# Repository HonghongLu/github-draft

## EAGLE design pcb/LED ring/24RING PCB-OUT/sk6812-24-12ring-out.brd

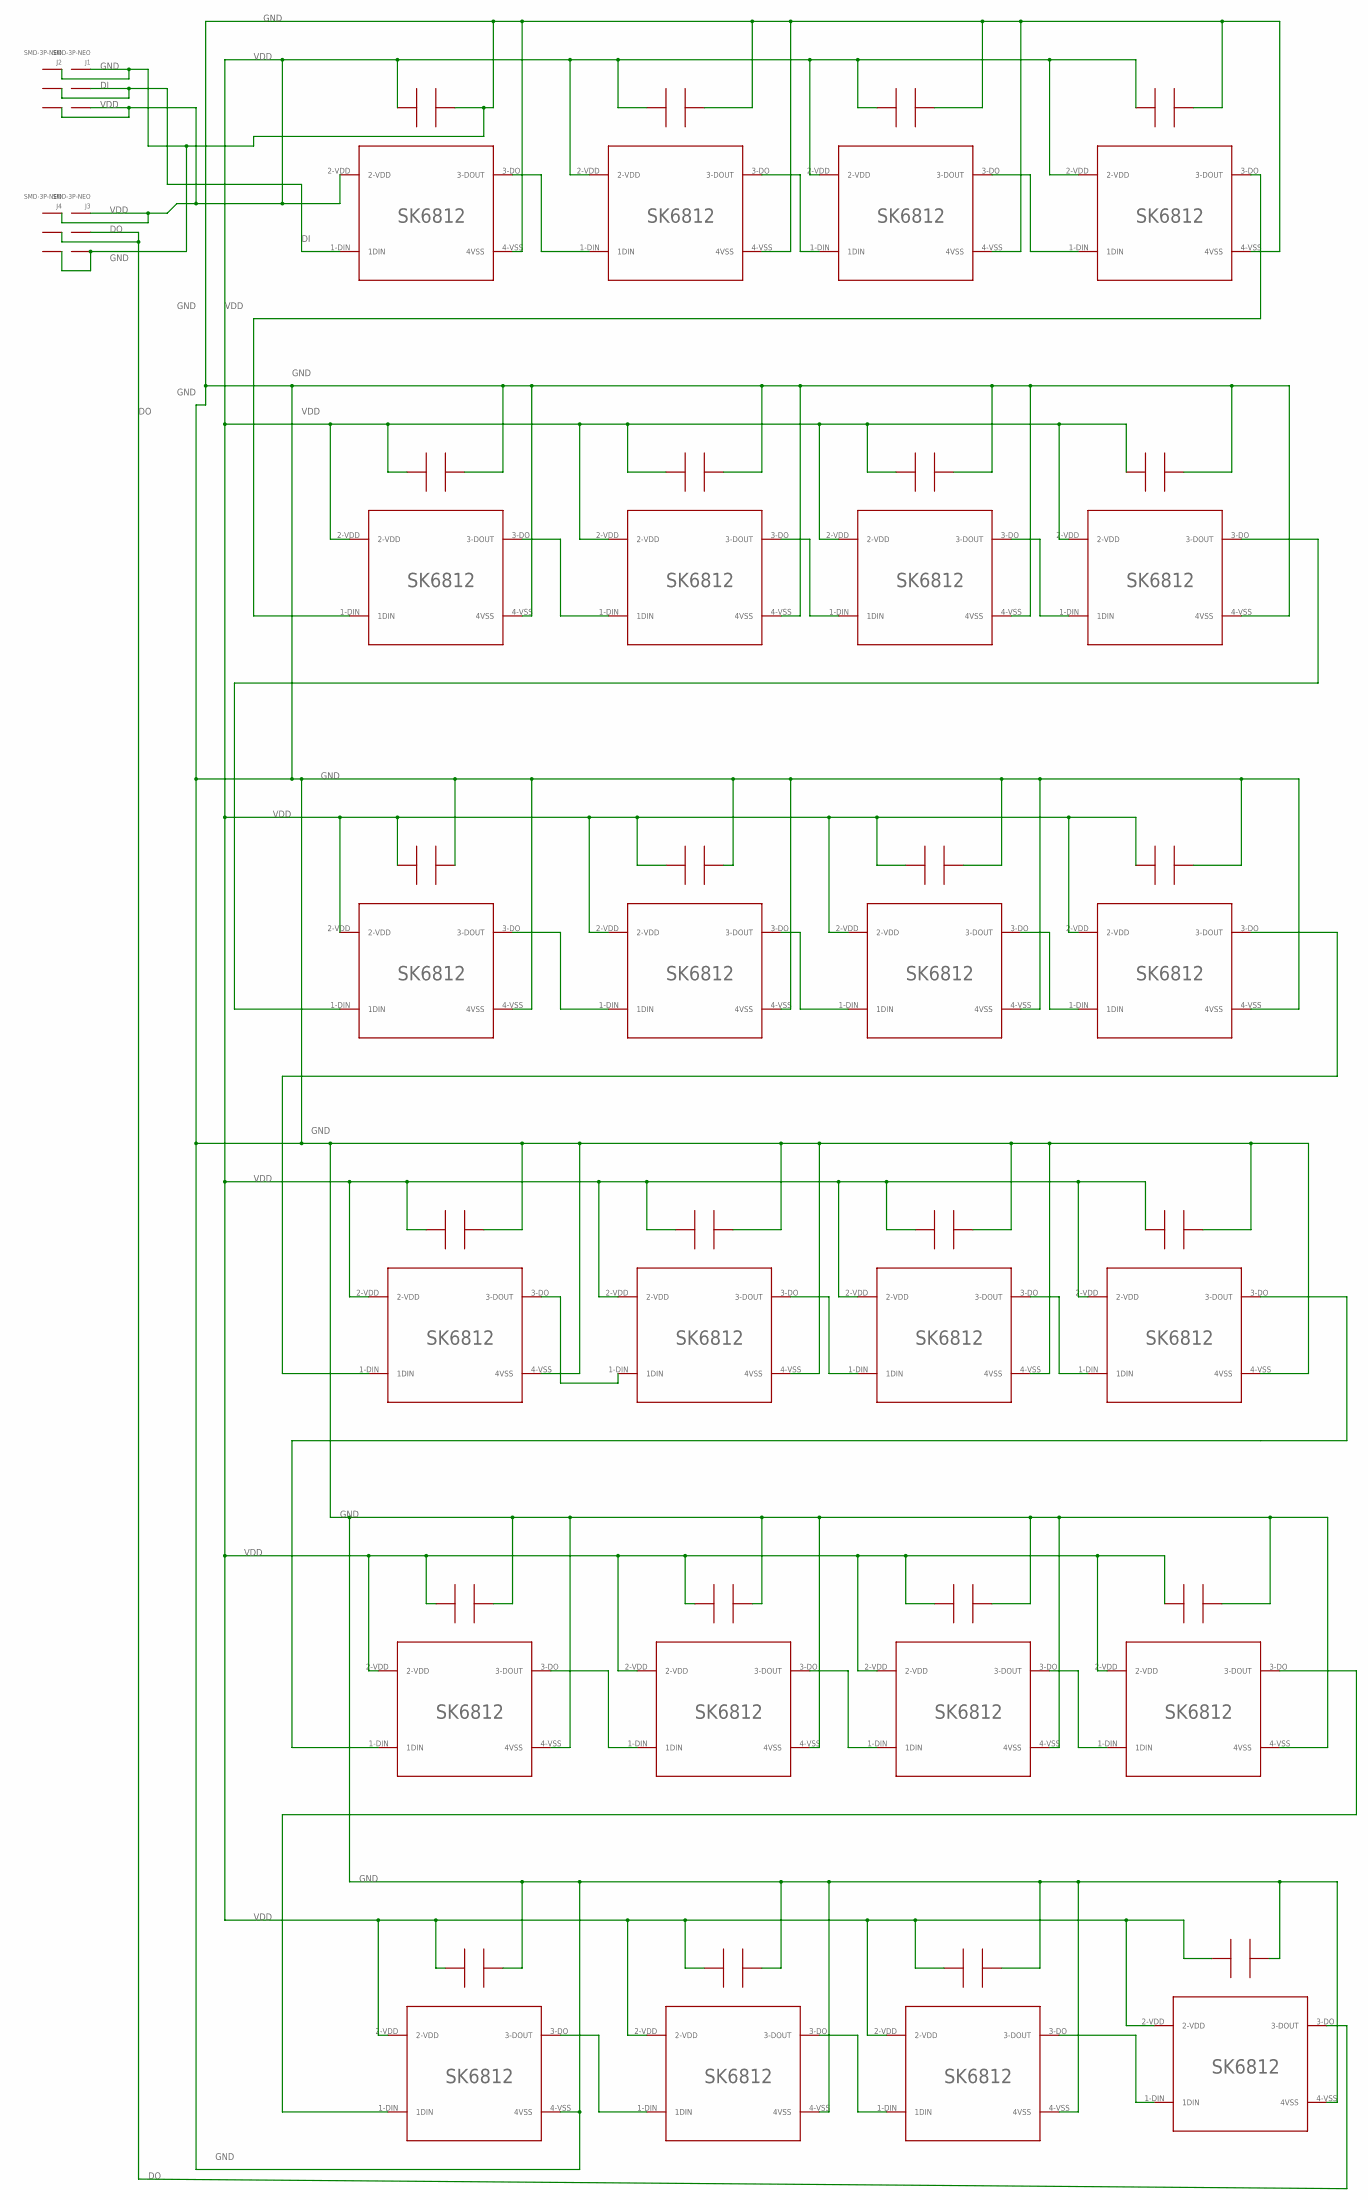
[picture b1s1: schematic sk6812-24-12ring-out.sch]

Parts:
D1, D2, D3, D4, D5, D6, D7, D8, D9, D10, D11, D12, D13, D14, D15, D16, D17, D18, D19, D20, D21, D22, D23, D24: SK6812-S-C; SMD4020+0402C
J1, J2, J3, J4: SMD-3P-NEO; SMD-3P-2.0

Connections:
DI: D1.1-DIN (1DIN), J1.P$2 (2), J2.P$2 (2)
DO: D24.3-DO (3-DOUT), J3.P$2 (2), J4.P$2 (2)
DO01: D1.3-DO (3-DOUT), D2.1-DIN (1DIN)
DO02: D2.3-DO (3-DOUT), D3.1-DIN (1DIN)
DO03: D3.3-DO (3-DOUT), D4.1-DIN (1DIN)
DO04: D4.3-DO (3-DOUT), D5.1-DIN (1DIN)
DO05: D5.3-DO (3-DOUT), D6.1-DIN (1DIN)
DO06: D6.3-DO (3-DOUT), D7.1-DIN (1DIN)
DO07: D7.3-DO (3-DOUT), D8.1-DIN (1DIN)
DO08: D8.3-DO (3-DOUT), D9.1-DIN (1DIN)
DO10: D10.3-DO (3-DOUT), D11.1-DIN (1DIN)
DO11: D11.3-DO (3-DOUT), D12.1-DIN (1DIN)
DO12: D12.3-DO (3-DOUT), D13.1-DIN (1DIN)
DO13: D13.3-DO (3-DOUT), D14.1-DIN (1DIN)
DO14: D14.3-DO (3-DOUT), D15.1-DIN (1DIN)
DO15: D15.3-DO (3-DOUT), D16.1-DIN (1DIN)
DO16: D16.3-DO (3-DOUT), D17.1-DIN (1DIN)
DO18: D18.3-DO (3-DOUT), D19.1-DIN (1DIN)
DO19: D19.3-DO (3-DOUT), D20.1-DIN (1DIN)
DO20: D20.3-DO (3-DOUT), D21.1-DIN (1DIN)
DO21: D21.3-DO (3-DOUT), D22.1-DIN (1DIN)
DO23: D23.3-DO (3-DOUT), D24.1-DIN (1DIN)
GND: D1.4-VSS (4VSS), D1.5-C-VSS (C-VSS), D2.4-VSS (4VSS), D2.5-C-VSS (C-VSS), D3.4-VSS (4VSS), D3.5-C-VSS (C-VSS), D4.4-VSS (4VSS), D4.5-C-VSS (C-VSS), D5.4-VSS (4VSS), D5.5-C-VSS (C-VSS), D6.4-VSS (4VSS), D6.5-C-VSS (C-VSS), D7.4-VSS (4VSS), D7.5-C-VSS (C-VSS), D8.4-VSS (4VSS), D8.5-C-VSS (C-VSS), D9.4-VSS (4VSS), D9.5-C-VSS (C-VSS), D10.4-VSS (4VSS), D10.5-C-VSS (C-VSS), D11.4-VSS (4VSS), D11.5-C-VSS (C-VSS), D12.4-VSS (4VSS), D12.5-C-VSS (C-VSS), D13.4-VSS (4VSS), D13.5-C-VSS (C-VSS), D14.4-VSS (4VSS), D14.5-C-VSS (C-VSS), D15.4-VSS (4VSS), D15.5-C-VSS (C-VSS), D16.4-VSS (4VSS), D16.5-C-VSS (C-VSS), D17.4-VSS (4VSS), D17.5-C-VSS (C-VSS), D18.4-VSS (4VSS), D18.5-C-VSS (C-VSS), D19.4-VSS (4VSS), D19.5-C-VSS (C-VSS), D20.4-VSS (4VSS), D20.5-C-VSS (C-VSS), D21.4-VSS (4VSS), D21.5-C-VSS (C-VSS), D22.4-VSS (4VSS), D22.5-C-VSS (C-VSS), D23.4-VSS (4VSS), D23.5-C-VSS (C-VSS), D24.4-VSS (4VSS), D24.5-C-VSS (C-VSS), J1.P$3 (3), J2.P$3 (3), J3.P$1 (1), J4.P$1 (1)
unnamed: D22.3-DO (3-DOUT), D23.1-DIN (1DIN)
unnamed: D17.3-DO (3-DOUT), D18.1-DIN (1DIN)
unnamed: D9.3-DO (3-DOUT), D10.1-DIN (1DIN)
VDD: D1.2-VDD, D1.6-C-VDD (C-VDD), D2.2-VDD, D2.6-C-VDD (C-VDD), D3.2-VDD, D3.6-C-VDD (C-VDD), D4.2-VDD, D4.6-C-VDD (C-VDD), D5.2-VDD, D5.6-C-VDD (C-VDD), D6.2-VDD, D6.6-C-VDD (C-VDD), D7.2-VDD, D7.6-C-VDD (C-VDD), D8.2-VDD, D8.6-C-VDD (C-VDD), D9.2-VDD, D9.6-C-VDD (C-VDD), D10.2-VDD, D10.6-C-VDD (C-VDD), D11.2-VDD, D11.6-C-VDD (C-VDD), D12.2-VDD, D12.6-C-VDD (C-VDD), D13.2-VDD, D13.6-C-VDD (C-VDD), D14.2-VDD, D14.6-C-VDD (C-VDD), D15.2-VDD, D15.6-C-VDD (C-VDD), D16.2-VDD, D16.6-C-VDD (C-VDD), D17.2-VDD, D17.6-C-VDD (C-VDD), D18.2-VDD, D18.6-C-VDD (C-VDD), D19.2-VDD, D19.6-C-VDD (C-VDD), D20.2-VDD, D20.6-C-VDD (C-VDD), D21.2-VDD, D21.6-C-VDD (C-VDD), D22.2-VDD, D22.6-C-VDD (C-VDD), D23.2-VDD, D23.6-C-VDD (C-VDD), D24.2-VDD, D24.6-C-VDD (C-VDD), J1.P$1 (1), J2.P$1 (1), J3.P$3 (3), J4.P$3 (3)

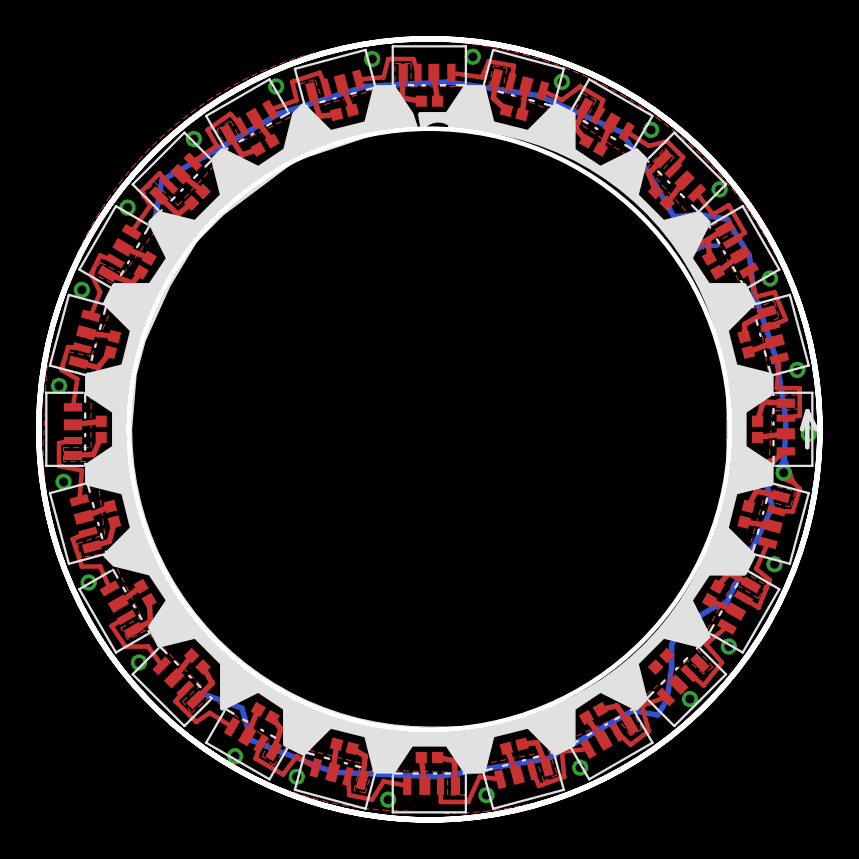
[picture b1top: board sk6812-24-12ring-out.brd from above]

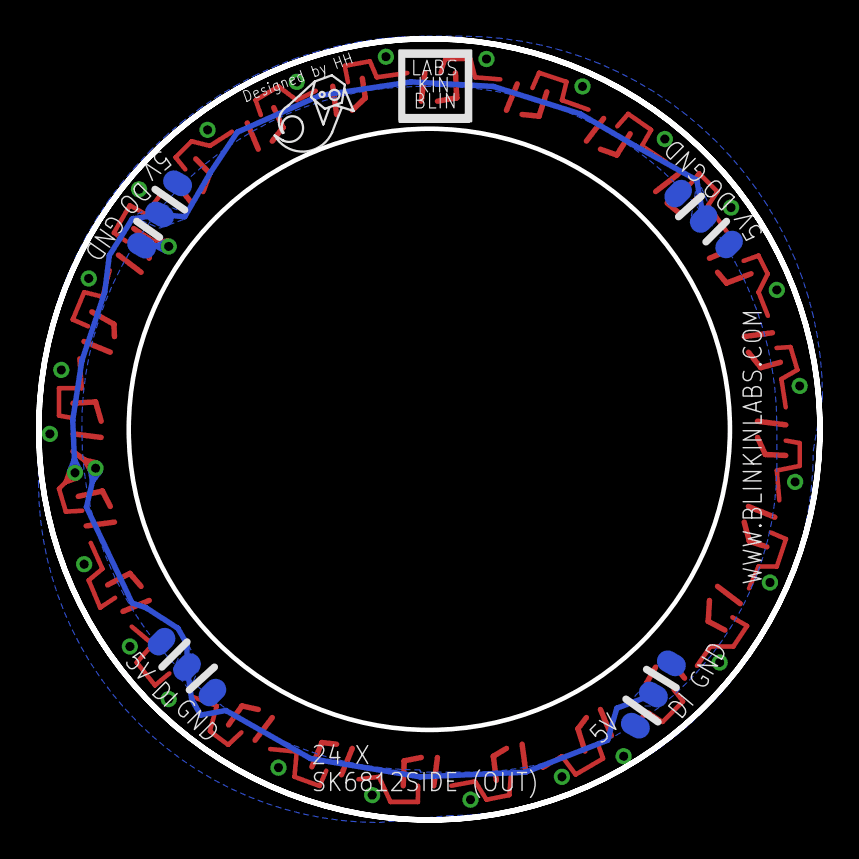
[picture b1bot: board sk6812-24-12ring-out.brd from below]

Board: 2 copper layers, 43.4 x 43.4 mm, 30 parts (6 on the bottom side), 27 nets.

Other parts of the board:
U$1: CRAZYCAT(M)
U$2: LOGO(M)

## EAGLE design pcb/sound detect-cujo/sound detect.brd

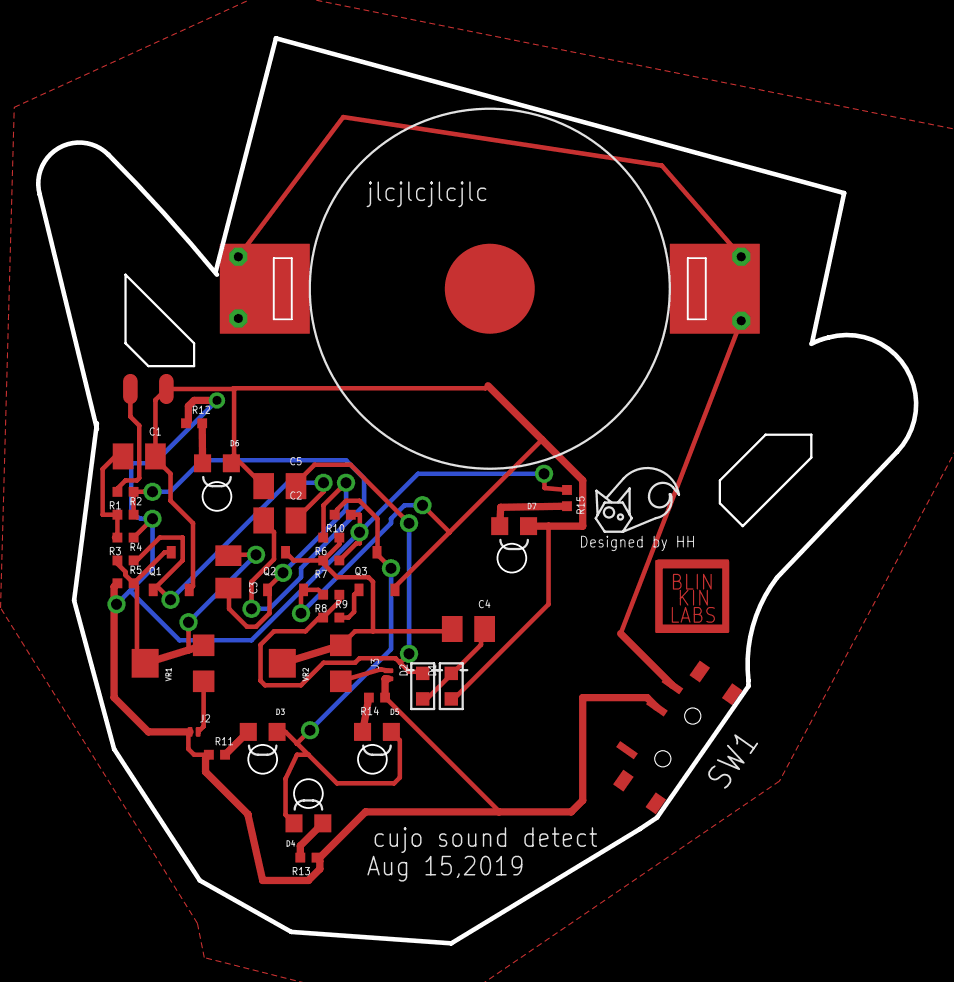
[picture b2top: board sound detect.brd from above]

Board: 2 copper layers, 48.8 x 50.3 mm, 40 parts (0 on the bottom side), 21 nets.

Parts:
C1: 10uF,0805; CAP-0805C-LEVELB
C2, C3, C4, C5: 1uF,0805; CAP-0805C-LEVELB
D1, D2: 1N4148-SOD523; SOD523
D3, D4, D5: 0603side-white; SMD-0603-LED-SIDE
D6, D7: 0603SIDELED-uv; SMD-0603-LED-SIDE
J1: SMD-PADS-2P; SMD-2P-2.0
J2, J3: SHORT_PAD; SHORTPAD
J4: CR2032-THR; CR2032-SMD
Q1, Q2, Q3: MMBT2222A; SOT23-3
R1, R2, R10: 1.2k,0402; RES-0402R-REFLOW
R3: 100R,0402; RES-0402R-REFLOW
R4, R6: 1M,0402; RES-0402R-REFLOW
R5, R7: 51k,0402; RES-0402R-REFLOW
R8: 100k,0402; RES-0402R-REFLOW
R9: 39k,0402; RES-0402R-REFLOW
R11, R12, R13, R14, R15: 510,0402; RES-0402R-REFLOW
SW1: SLIDE-MSK12C01-07; SLIDE-SW-MSK-12C01-07
U$2: CUJO(5050)-MASK-BOT
U$3: CRAZYCAT(M)
U$4: LOGO(M-T)
VR1, VR2: VG039NCHXTB204,200kVR; SMD-3638

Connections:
GND: C1.P$1, C5.P$2, D1.A, D6.C, D7.C, J1.P$1, J4.-, Q1.P$2, Q2.P$2, Q3.P$2, R8.P$1
MIC+: J1.P$2, R1.P$1
unnamed: C2.P$2, R1.P$2, R2.P$1
unnamed: C2.P$1, Q1.P$1, R4.P$1
unnamed: C3.P$1, Q2.P$1, R6.P$1
unnamed: C1.P$2, R2.P$2, R3.P$1
unnamed: J4.+, J4.+1, J4.++, J4.++1, J4.P$1, J4.P$2, J4.P$3, J4.P$4, SW1.POS2
unnamed: C4.P$1, D1.K, D2.A
unnamed: Q3.P$1, R9.P$1
unnamed: C5.P$1, D2.K, R8.P$2, R9.P$2
unnamed: C4.P$2, Q2.P$3, R6.P$2, R7.P$1, VR2.P$1, VR2.P$2
unnamed: D7.A, R15.P$1
unnamed: D3.C, D4.C, D5.C, Q3.P$3, R10.P$1
unnamed: D3.A, R11.P$1
unnamed: D6.A, R12.P$1
unnamed: D4.A, R13.P$1
unnamed: J2.P$1, VR1.P$3
unnamed: D5.A, R14.P$1
unnamed: C3.P$2, Q1.P$3, R4.P$2, R5.P$1, VR1.P$1, VR1.P$2
unnamed: J3.P$1, VR2.P$3
VCC: J2.P$2, J3.P$2, R3.P$2, R5.P$2, R7.P$2, R10.P$2, R11.P$2, R12.P$2, R13.P$2, R14.P$2, R15.P$2, SW1.COM

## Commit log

2017-10-25 just a holder for the pogo pins
    i printed it on up mini.
2017-11-04 this is the holder for blinkytile
    accessory: M3 screws
    stl file, up mini printed, 4minutes, material: pla.
    purpose: to hold the blinkytile pcb and mount it to the surface like wood etc...
2017-11-04 blinkytile holder photo
    blinkytile holder-M3 screw
2017-11-04 blinkytile_holder_holder 2-M3screws
    photos for the holder
2017-11-28 add file folder
2017-11-28 add folder
2018-01-06 add sk6812side*24ring pcb eagle files to led ring
    sk6812side pcb
    size 42*42mm
    product list
    face in
    https://shop.blinkinlabs.com/collections/leds/products/led-ring-with-24-right-angle-leds-inwards-facing
    face out
2018-10-16 move the files into 8by8 folder
2018-10-16 change the mounting holes location
2018-11-16 add 4mm cable maganet clip drawing
2018-11-16 rename
2019-02-01 milk frother stand
    it is designed to work with PRODUKT, Milk-frother from Ikea. I designed this tools for the frother work with most of the cups and glasses in my kitchen. https://www.instagram.com/p/BtU-5IWnOer/
2019-06-25 upload ring_out 3d drawing
2019-06-25 3d drawing
    upload the ring out 3d drawing
2019-06-25 ring_in_3d drawing
    upload 3d drawing
2019-06-25 drawing
    ring_out drawing in pdf
2019-06-25 drawing
    ring_in drawing in pdf
2019-06-25 drawing
    pdf drawing update
2019-06-25 drawing
    pdf drawing
2019-06-25 drawing
    drawing in pdf
2019-06-26 clip0626
    add support for the clip, snap the magnet instead glue it.
2019-08-22 Create sound detect cujo badge
2019-08-22 sound detect board
    sound detect board original from one part of toy circuit. It is analog circuit only.
2020-04-09 1.27-1.27-2X5
    1.27mm pitch to 1.27mm pitch, 2X5 pogo pin
    the pcb convert the 1.27 pogo pin to 2.54mm pitch to 2.54mm pitch 2X5 header.
    parts--
    pcb, 1.6mm(can be other thickness) FR4 HASL double layer
    R50-2W7, pogo pin socket solder on to the pcb
    P50-XX, pogo pins to push inside the pogo pin socket.
2020-04-09 1.27-1.27-2X5pogo pin photo
2020-12-02 Create led filament v1.step
    add filament 3d file
2020-12-02 Create led filament spec.pdf
    add filament datasheet
2021-01-13 add the reball stencil file for QL-EOS
    stencil thickness 0.2mm, normal laser cut. The stencil can work with the reball tool.
    BGA part:
    0.4mm pitch, 8*8 BGA, ball size 0.2mm or 0.25mm, recommend 0.2mm leadfree ball, hot plate process, remember use super thin flux on the BGA
2021-01-13 fdm printing 10mm strips holder for sofa
    LED Strip holder
2021-03-04 Create fusion file backup
2021-04-23 blinkytape controller stencil
    stencil frame: 250mm*250mm 5mm acrylic
    pcb panels: Rev I
2021-05-07 stencil frame
    stencil frame
2021-06-19 convert pc 120mm pc fan to solder Fume Extractor
    convert pc 120mm pc fan to solder Fume Extractor
2021-07-07 move the file into the folder
2021-07-12 add the 8X8 pixel images for reference
2021-07-14 add 18650 battery case
2021-07-16 add cat ear glasses
2021-07-21 add btc case 3d files
2021-07-26 add AAA case and fan stand
2021-07-26 case for the caliper
2021-08-02 add luzhanqi files
2021-09-29 add 3d files
2021-09-29 add btc pic
2021-11-16 add 1.27-2.0-2.54 pogo pin perfboard
    HASL with 0.8mm thickness
2023-01-08 add universal test rig_fdm printing parts drawing
    test jig is from https://www.aliexpress.com/item/1005001779451202.html?gatewayAdapt=glo2nld
    it is 180X160mm pcb universal test jig with 4layer acrylic panels.
    example pcba under test: 10mmX24mm with usb C pcb, pogo pins are 075 types, test points are 2mm pitch.
2023-01-08 add remarks
    add remarks
2023-01-08 update the drawing
    update the drawing
2023-01-08 add stl file
    add stil file
2023-03-21 add touch sensor light controller
    add touch sensor light controller
2023-03-21 touch sensor light controller
    add pcb assembly photo
2023-03-21 Create 3d drawing_screenshot.png
    add drawing screenshot
2023-03-21 Update 3d drawing_screenshot.png
    add screenshot
2023-03-21 Update 3d drawing_screenshot.png
    change image size
2023-03-21 add photos
    add photos
2023-03-21 Create Schematic_LED capsensor board_2023-03-21.jpg
    add schematic screenshot
2023-03-21 update schematic
    update schematic
2023-03-21 add 3d drawing screenshot
    add 3d drawing screenshot
2023-03-22 update the R1 value
    update the R1 value
2023-03-22 updated the schematic description
    updated the schematic description
2023-03-22 add compnent datasheet
    add compnent datasheet
2023-03-24 add terminal block internal photo and update gerber file without jlc
    add terminal block internal photo and update gerber file without jlc
2023-05-02 add some the perfboard images
